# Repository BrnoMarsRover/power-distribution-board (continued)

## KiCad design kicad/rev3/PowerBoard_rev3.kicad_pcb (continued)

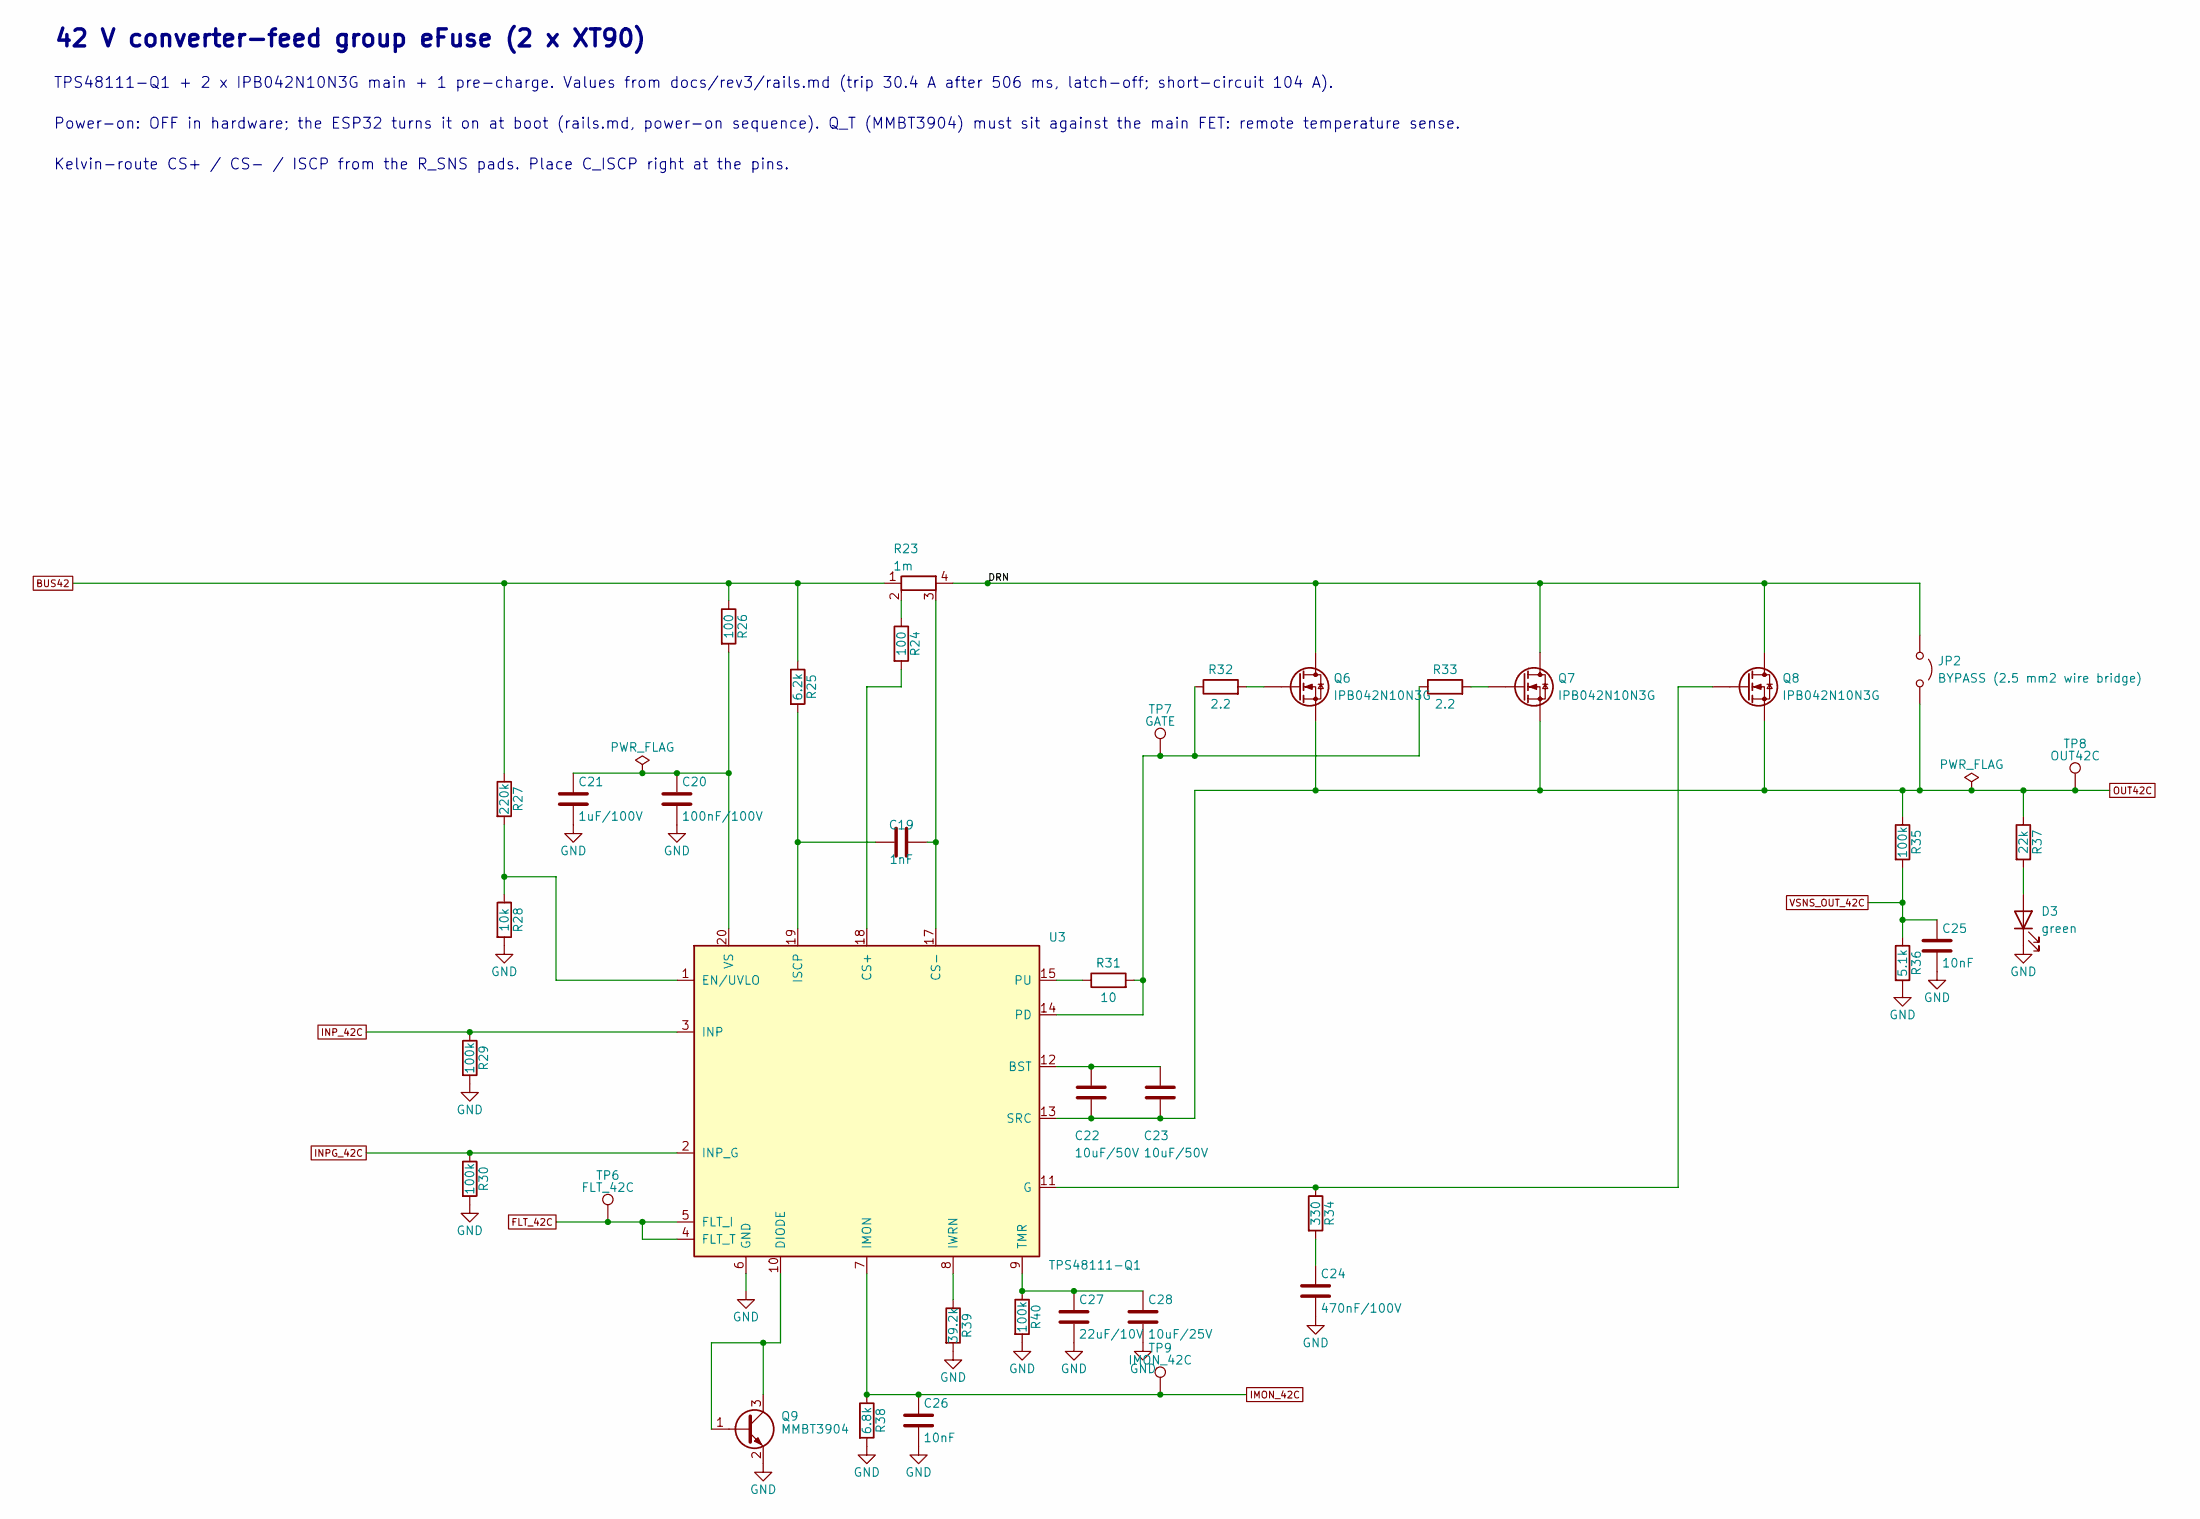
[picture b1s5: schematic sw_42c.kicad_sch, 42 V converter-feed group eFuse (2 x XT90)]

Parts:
C19: 1nF; C_0603_1608Metric_Pad1.08x0.95mm_HandSolder; MPN C0603C102J5GACTU
C20: 100nF/100V; C_0603_1608Metric_Pad1.08x0.95mm_HandSolder; MPN CL10B104KC8NNNC
C21: 1uF/100V; C_1206_3216Metric_Pad1.33x1.80mm_HandSolder; MPN GRM31CR72A105KA01L
C22, C23: 10uF/50V; C_1210_3225Metric_Pad1.33x2.70mm_HandSolder; MPN CL32B106KBJNNNE
C24: 470nF/100V; C_1206_3216Metric_Pad1.33x1.80mm_HandSolder; MPN C1206C474K1RACTU
C25, C26: 10nF; C_0603_1608Metric_Pad1.08x0.95mm_HandSolder; MPN CL10B103KB8NNNC
C27: 22uF/10V; C_1206_3216Metric_Pad1.33x1.80mm_HandSolder; MPN CL31B226KPHNNNE
C28: 10uF/25V; C_1206_3216Metric_Pad1.33x1.80mm_HandSolder; MPN CL31A106KAHNNNE
D3: green; LED_0805_2012Metric_Pad1.15x1.40mm_HandSolder; MPN APT2012SGC
JP2: BYPASS (2.5 mm2 wire bridge); WireBridge_2.5mm2_P7.62mm; MPN none: solid copper wire bridge, fitted 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
Q6, Q7, Q8: IPB042N10N3G; TO-263-2; MPN IPB042N10N3GATMA1
Q9: MMBT3904; SOT-23; MPN MMBT3904LT1G
R23: 1m; R_Bourns_CSS2H-2512_Kelvin; MPN CSS2H-2512R-1L00F
R24, R26: 100; R_0603_1608Metric_Pad0.98x0.95mm_HandSolder; MPN RC0603FR-07100RL
R25: 6.2k; R_0603_1608Metric_Pad0.98x0.95mm_HandSolder; MPN RC0603FR-076K2L
R27: 220k; R_0603_1608Metric_Pad0.98x0.95mm_HandSolder; MPN RC0603FR-07220KL
R28: 10k; R_0603_1608Metric_Pad0.98x0.95mm_HandSolder; MPN RC0603FR-0710KL
R29, R30, R35, R40: 100k; R_0603_1608Metric_Pad0.98x0.95mm_HandSolder; MPN RC0603FR-07100KL
R31: 10; R_0603_1608Metric_Pad0.98x0.95mm_HandSolder; MPN RC0603FR-0710RL
R32, R33: 2.2; R_0603_1608Metric_Pad0.98x0.95mm_HandSolder; MPN RC0603FR-072R2L
R34: 330; R_0603_1608Metric_Pad0.98x0.95mm_HandSolder; MPN RC0603FR-07330RL
R36: 5.1k; R_0603_1608Metric_Pad0.98x0.95mm_HandSolder; MPN RC0603FR-075K1L
R37: 22k; R_1206_3216Metric_Pad1.30x1.75mm_HandSolder; MPN RC1206FR-0722KL
R38: 6.8k; R_0603_1608Metric_Pad0.98x0.95mm_HandSolder; MPN RC0603FR-076K8L
R39: 39.2k; R_0603_1608Metric_Pad0.98x0.95mm_HandSolder; MPN RC0603FR-1339K2L
TP6: FLT_42C; TestPoint_Pad_D1.5mm; MPN none: PCB pad
TP7: GATE; TestPoint_Pad_D1.5mm; MPN none: PCB pad
TP8: OUT42C; TestPoint_Pad_D1.5mm; MPN none: PCB pad
TP9: IMON_42C; TestPoint_Pad_D1.5mm; MPN none: PCB pad
U3: TPS48111-Q1; TI_DGX0019A_VSSOP-19; MPN TPS48111LQDGXRQ1

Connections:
/42 V converter-feed group eFuse (2 x XT90)/DRN: JP2.1 (A), Q6.2 (D), Q7.2 (D), Q8.2 (D), R23.4
BUS42: R23.1, R25.1, R26.1, R27.1; also elsewhere on the board
FLT_42C: TP6.1, U3.4 (FLT_T), U3.5 (FLT_I); also elsewhere on the board
GND: C20.2, C21.2, C24.2, C25.2, C26.2, C27.2, C28.2, D3.1 (K), Q9.2 (E), R28.2, R29.2, R30.2, R36.2, R38.2, R39.2, R40.2, U3.6 (GND); also elsewhere on the board
IMON_42C: C26.1, R38.1, TP9.1, U3.7 (IMON); also elsewhere on the board
INPG_42C: R30.1, U3.2 (INP_G); also elsewhere on the board
INP_42C: R29.1, U3.3 (INP); also elsewhere on the board
unnamed: C24.1, R34.2
unnamed: D3.2 (A), R37.2
unnamed: Q6.1 (G), R32.2
unnamed: Q7.1 (G), R33.2
unnamed: Q8.1 (G), R34.1, U3.11 (G)
unnamed: Q9.1 (B), Q9.3 (C), U3.10 (DIODE)
unnamed: R23.2, R24.1
unnamed: C22.1, C23.1, U3.12 (BST)
unnamed: R24.2, U3.18 (CS+)
unnamed: C19.2, R23.3, U3.17 (CS-)
unnamed: R27.2, R28.1, U3.1 (EN/UVLO)
unnamed: C19.1, R25.2, U3.19 (ISCP)
unnamed: R39.1, U3.8 (IWRN)
unnamed: R31.2, R32.1, R33.1, TP7.1, U3.14 (PD)
unnamed: R31.1, U3.15 (PU)
unnamed: C27.1, C28.1, R40.1, U3.9 (TMR)
unnamed: C20.1, C21.1, R26.2, U3.20 (VS)
OUT42C: C22.2, C23.2, JP2.2 (B), Q6.3 (S), Q7.3 (S), Q8.3 (S), R35.1, R37.1, TP8.1, U3.13 (SRC); also elsewhere on the board
VSNS_OUT_42C: C25.1, R35.2, R36.1; also elsewhere on the board

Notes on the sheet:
42 V converter-feed group eFuse (2 x XT90)
Power-on: OFF in hardware; the ESP32 turns it on at boot (rails.md, power-on sequence). Q_T (MMBT3904) must sit against the main FET: remote temperature sense.
Kelvin-route CS+ / CS- / ISCP from the R_SNS pads. Place C_ISCP right at the pins.
TPS48111-Q1 + 2 x IPB042N10N3G main + 1 pre-charge. Values from docs/rev3/rails.md (trip 30.4 A after 506 ms, latch-off; short-circuit 104 A).

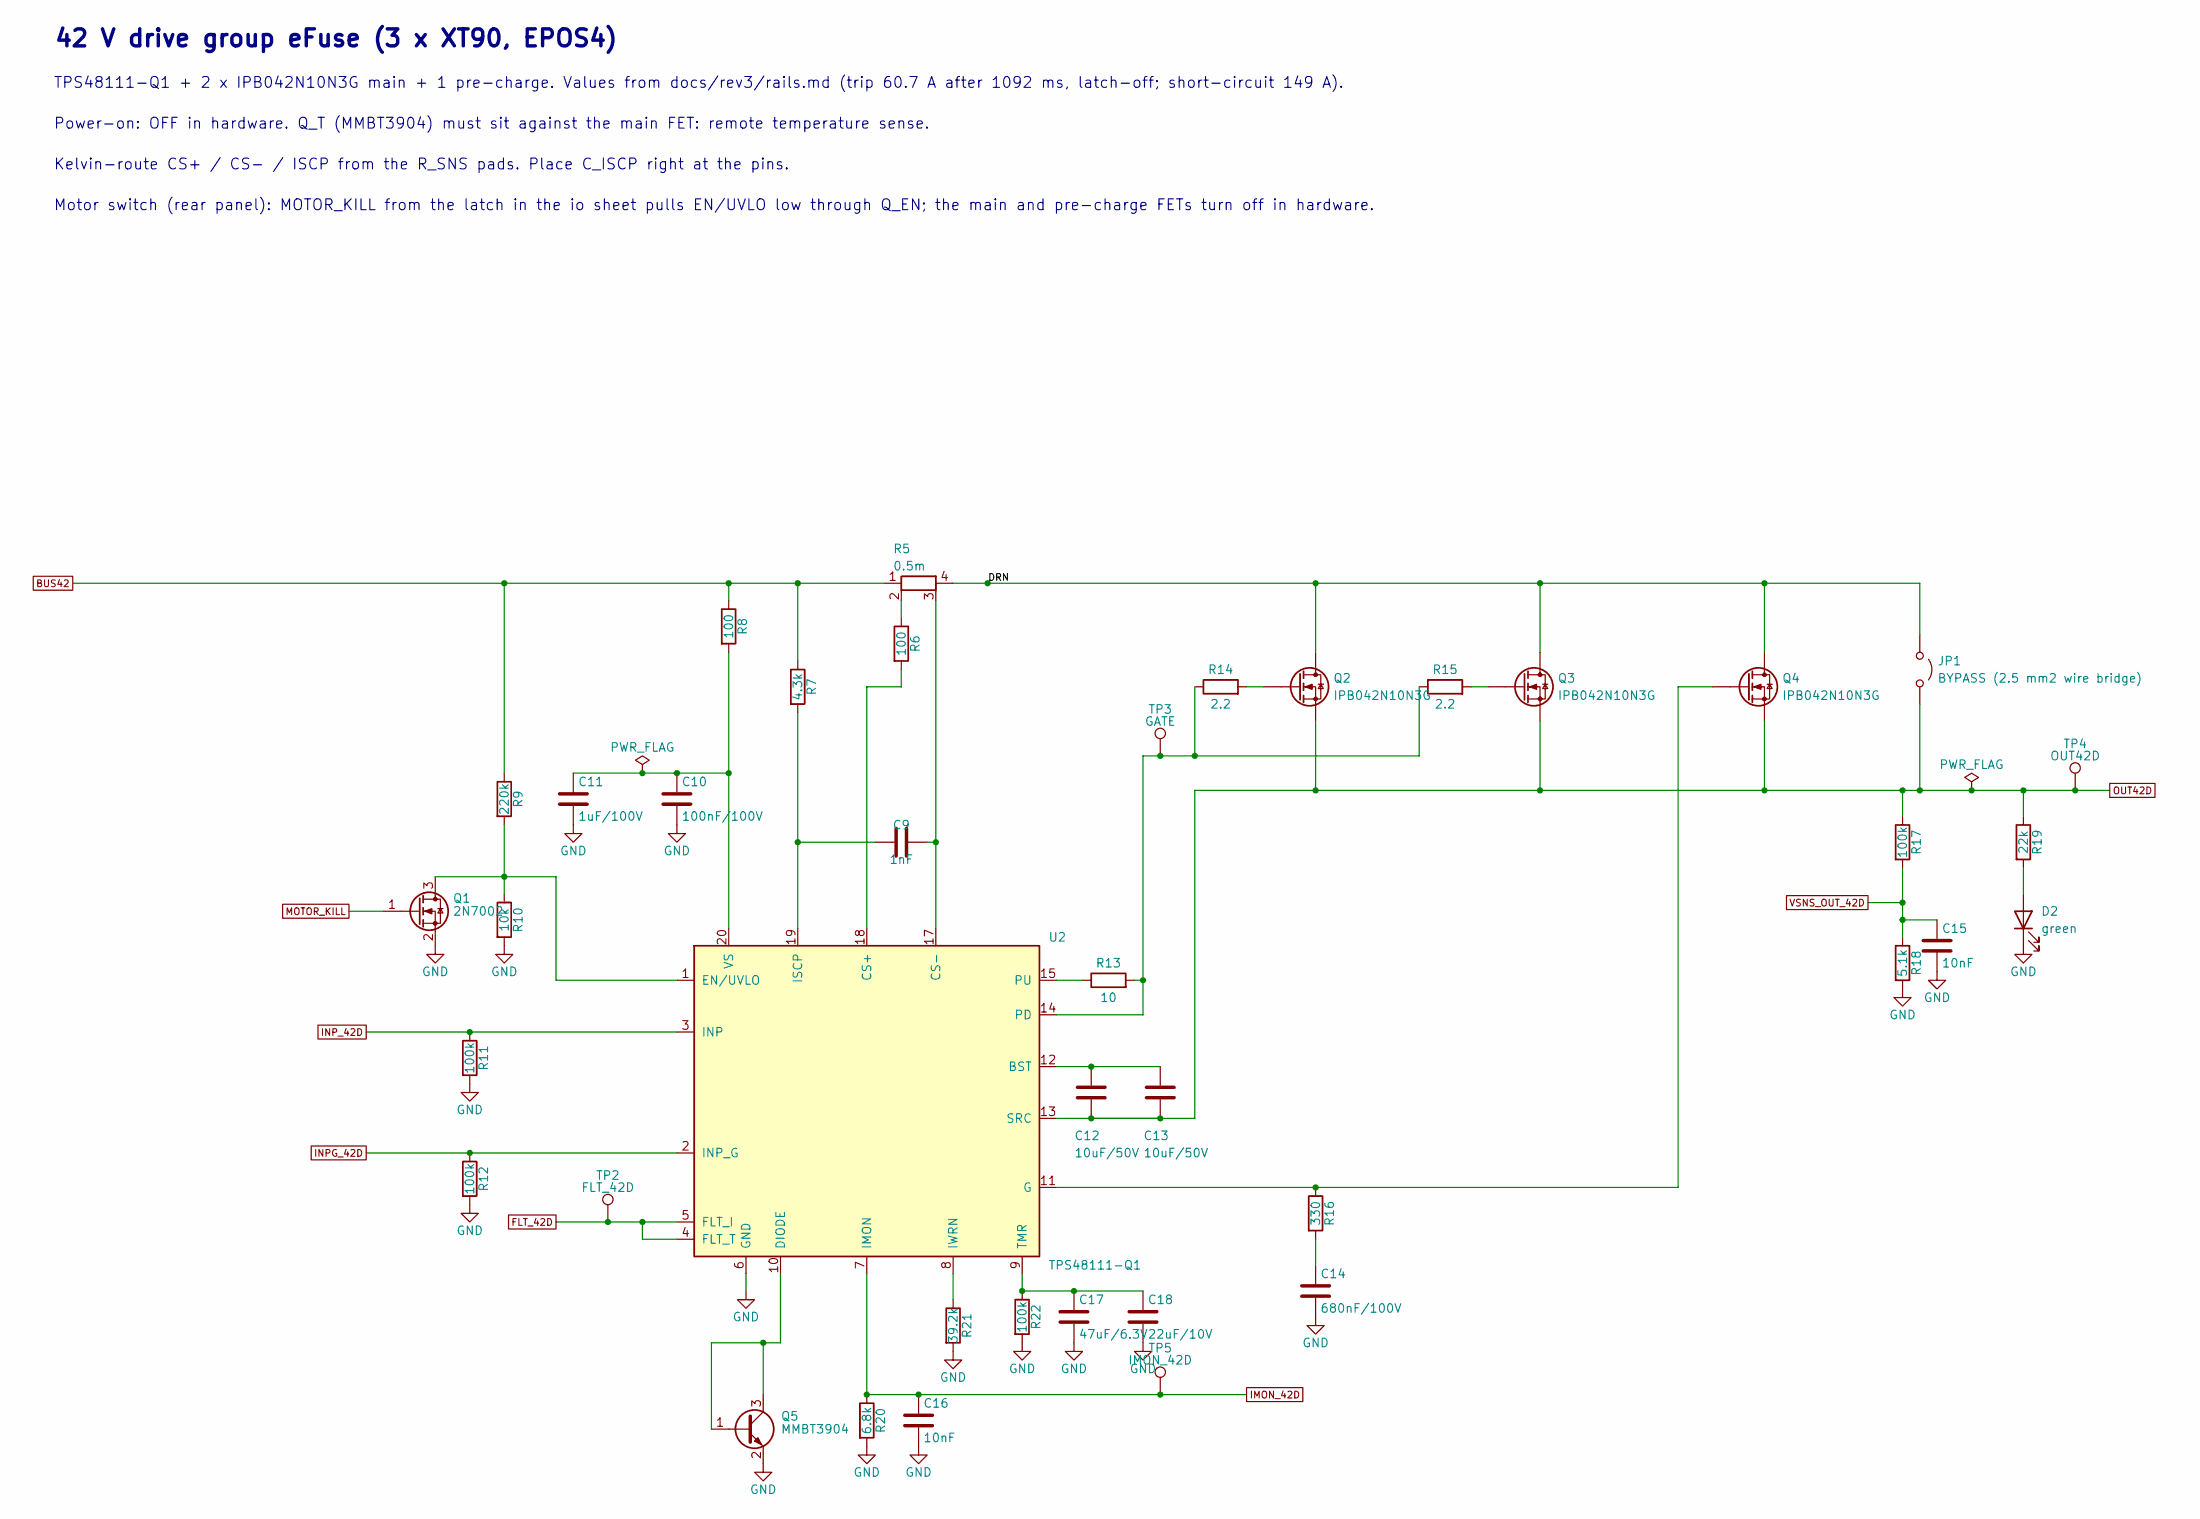
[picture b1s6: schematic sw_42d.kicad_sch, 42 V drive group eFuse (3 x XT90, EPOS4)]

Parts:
C9: 1nF; C_0603_1608Metric_Pad1.08x0.95mm_HandSolder; MPN C0603C102J5GACTU
C10: 100nF/100V; C_0603_1608Metric_Pad1.08x0.95mm_HandSolder; MPN CL10B104KC8NNNC
C11: 1uF/100V; C_1206_3216Metric_Pad1.33x1.80mm_HandSolder; MPN GRM31CR72A105KA01L
C12, C13: 10uF/50V; C_1210_3225Metric_Pad1.33x2.70mm_HandSolder; MPN CL32B106KBJNNNE
C14: 680nF/100V; C_1206_3216Metric_Pad1.33x1.80mm_HandSolder; MPN C3216X7R2A684K160AA
C15, C16: 10nF; C_0603_1608Metric_Pad1.08x0.95mm_HandSolder; MPN CL10B103KB8NNNC
C17: 47uF/6.3V; C_1206_3216Metric_Pad1.33x1.80mm_HandSolder; MPN CL31A476MQHNNNE
C18: 22uF/10V; C_1206_3216Metric_Pad1.33x1.80mm_HandSolder; MPN CL31B226KPHNNNE
D2: green; LED_0805_2012Metric_Pad1.15x1.40mm_HandSolder; MPN APT2012SGC
JP1: BYPASS (2.5 mm2 wire bridge); WireBridge_2.5mm2_P7.62mm; MPN none: solid copper wire bridge, fitted 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
Q1: 2N7002; SOT-23; MPN 2N7002LT1G
Q2, Q3, Q4: IPB042N10N3G; TO-263-2; MPN IPB042N10N3GATMA1
Q5: MMBT3904; SOT-23; MPN MMBT3904LT1G
R5: 0.5m; R_Bourns_CSS2H-2512_Kelvin; MPN CSS2H-2512R-L500F
R6, R8: 100; R_0603_1608Metric_Pad0.98x0.95mm_HandSolder; MPN RC0603FR-07100RL
R7: 4.3k; R_0603_1608Metric_Pad0.98x0.95mm_HandSolder; MPN RC0603FR-074K3L
R9: 220k; R_0603_1608Metric_Pad0.98x0.95mm_HandSolder; MPN RC0603FR-07220KL
R10: 10k; R_0603_1608Metric_Pad0.98x0.95mm_HandSolder; MPN RC0603FR-0710KL
R11, R12, R17, R22: 100k; R_0603_1608Metric_Pad0.98x0.95mm_HandSolder; MPN RC0603FR-07100KL
R13: 10; R_0603_1608Metric_Pad0.98x0.95mm_HandSolder; MPN RC0603FR-0710RL
R14, R15: 2.2; R_0603_1608Metric_Pad0.98x0.95mm_HandSolder; MPN RC0603FR-072R2L
R16: 330; R_0603_1608Metric_Pad0.98x0.95mm_HandSolder; MPN RC0603FR-07330RL
R18: 5.1k; R_0603_1608Metric_Pad0.98x0.95mm_HandSolder; MPN RC0603FR-075K1L
R19: 22k; R_1206_3216Metric_Pad1.30x1.75mm_HandSolder; MPN RC1206FR-0722KL
R20: 6.8k; R_0603_1608Metric_Pad0.98x0.95mm_HandSolder; MPN RC0603FR-076K8L
R21: 39.2k; R_0603_1608Metric_Pad0.98x0.95mm_HandSolder; MPN RC0603FR-1339K2L
TP2: FLT_42D; TestPoint_Pad_D1.5mm; MPN none: PCB pad
TP3: GATE; TestPoint_Pad_D1.5mm; MPN none: PCB pad
TP4: OUT42D; TestPoint_Pad_D1.5mm; MPN none: PCB pad
TP5: IMON_42D; TestPoint_Pad_D1.5mm; MPN none: PCB pad
U2: TPS48111-Q1; TI_DGX0019A_VSSOP-19; MPN TPS48111LQDGXRQ1

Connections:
/42 V drive group eFuse (3 x XT90, EPOS4)/DRN: JP1.1 (A), Q2.2 (D), Q3.2 (D), Q4.2 (D), R5.4
BUS42: R5.1, R7.1, R8.1, R9.1; also elsewhere on the board
FLT_42D: TP2.1, U2.4 (FLT_T), U2.5 (FLT_I); also elsewhere on the board
GND: C10.2, C11.2, C14.2, C15.2, C16.2, C17.2, C18.2, D2.1 (K), Q1.2 (S), Q5.2 (E), R10.2, R11.2, R12.2, R18.2, R20.2, R21.2, R22.2, U2.6 (GND); also elsewhere on the board
IMON_42D: C16.1, R20.1, TP5.1, U2.7 (IMON); also elsewhere on the board
INPG_42D: R12.1, U2.2 (INP_G); also elsewhere on the board
INP_42D: R11.1, U2.3 (INP); also elsewhere on the board
MOTOR_KILL: Q1.1 (G); also elsewhere on the board
unnamed: C14.1, R16.2
unnamed: D2.2 (A), R19.2
unnamed: Q1.3 (D), R9.2, R10.1, U2.1 (EN/UVLO)
unnamed: Q2.1 (G), R14.2
unnamed: Q3.1 (G), R15.2
unnamed: Q4.1 (G), R16.1, U2.11 (G)
unnamed: Q5.1 (B), Q5.3 (C), U2.10 (DIODE)
unnamed: R5.2, R6.1
unnamed: C12.1, C13.1, U2.12 (BST)
unnamed: R6.2, U2.18 (CS+)
unnamed: C9.2, R5.3, U2.17 (CS-)
unnamed: C9.1, R7.2, U2.19 (ISCP)
unnamed: R21.1, U2.8 (IWRN)
unnamed: R13.2, R14.1, R15.1, TP3.1, U2.14 (PD)
unnamed: R13.1, U2.15 (PU)
unnamed: C17.1, C18.1, R22.1, U2.9 (TMR)
unnamed: C10.1, C11.1, R8.2, U2.20 (VS)
OUT42D: C12.2, C13.2, JP1.2 (B), Q2.3 (S), Q3.3 (S), Q4.3 (S), R17.1, R19.1, TP4.1, U2.13 (SRC); also elsewhere on the board
VSNS_OUT_42D: C15.1, R17.2, R18.1; also elsewhere on the board

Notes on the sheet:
Motor switch (rear panel): MOTOR_KILL from the latch in the io sheet pulls EN/UVLO low through Q_EN; the main and pre-charge FETs turn off in hardware.
TPS48111-Q1 + 2 x IPB042N10N3G main + 1 pre-charge. Values from docs/rev3/rails.md (trip 60.7 A after 1092 ms, latch-off; short-circuit 149 A).
Power-on: OFF in hardware. Q_T (MMBT3904) must sit against the main FET: remote temperature sense.
Kelvin-route CS+ / CS- / ISCP from the R_SNS pads. Place C_ISCP right at the pins.
42 V drive group eFuse (3 x XT90, EPOS4)

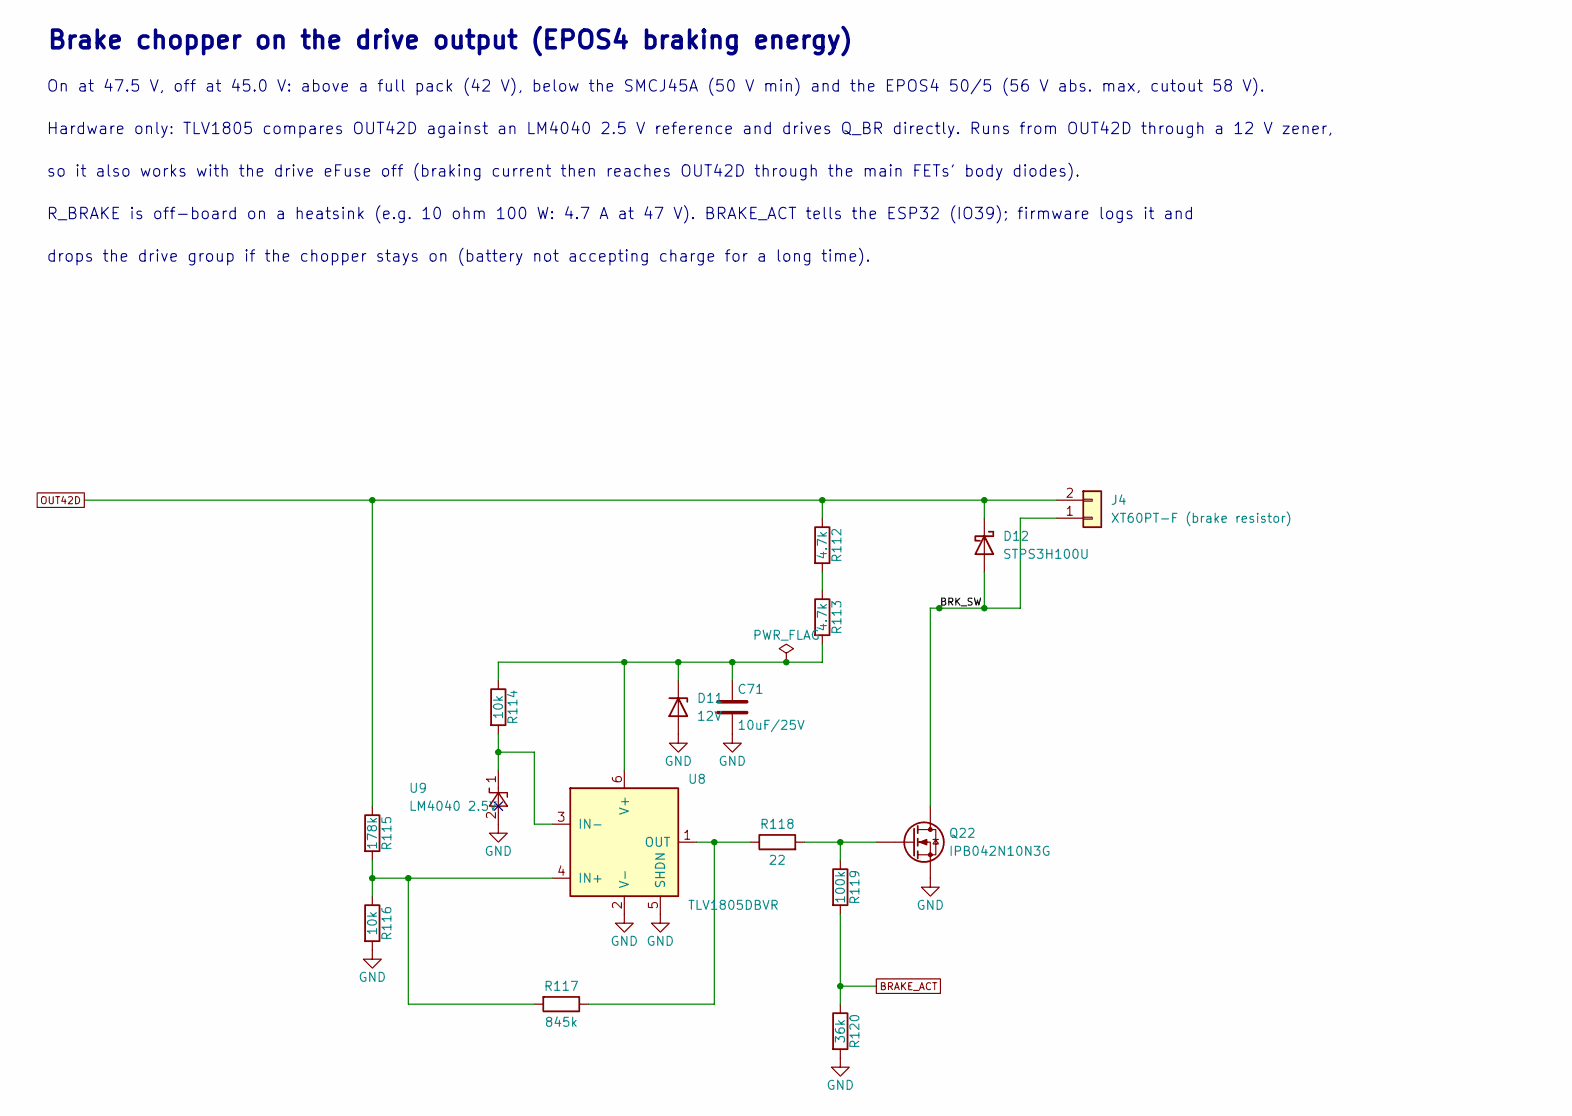
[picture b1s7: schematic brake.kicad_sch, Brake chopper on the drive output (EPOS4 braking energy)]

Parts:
C71: 10uF/25V; C_1206_3216Metric_Pad1.33x1.80mm_HandSolder; MPN CL31A106KAHNNNE
D11: 12V; D_SOD-123; MPN MMSZ5242BT1G
D12: STPS3H100U; D_SMB; MPN STPS3H100U
J4: XT60PT-F (brake resistor); AMASS_XT60-F_1x02_P7.20mm_Vertical; MPN XT60PT-F
Q22: IPB042N10N3G; TO-263-2; MPN IPB042N10N3GATMA1
R112, R113: 4.7k; R_1206_3216Metric_Pad1.30x1.75mm_HandSolder; MPN RC1206FR-074K7L
R114, R116: 10k; R_0603_1608Metric_Pad0.98x0.95mm_HandSolder; MPN RC0603FR-0710KL
R115: 178k; R_1206_3216Metric_Pad1.30x1.75mm_HandSolder; MPN RC1206FR-07178KL
R117: 845k; R_0603_1608Metric_Pad0.98x0.95mm_HandSolder; MPN RC0603FR-07845KL
R118: 22; R_0603_1608Metric_Pad0.98x0.95mm_HandSolder; MPN RC0603FR-0722RL
R119: 100k; R_0603_1608Metric_Pad0.98x0.95mm_HandSolder; MPN RC0603FR-07100KL
R120: 36k; R_0603_1608Metric_Pad0.98x0.95mm_HandSolder; MPN RC0603FR-0736KL
U8: TLV1805DBVR; SOT-23-6; MPN TLV1805DBVR
U9: LM4040 2.5V; SOT-23; MPN LM4040B25IDBZR

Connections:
/Brake chopper on the drive output (EPOS4 braking energy)/BRK_SW: D12.2 (A), J4.1 (-), Q22.2 (D)
BRAKE_ACT: R119.2, R120.1; also elsewhere on the board
GND: C71.2, D11.2 (A), Q22.3 (S), R116.2, R120.2, U8.2 (V-), U8.5 (SHDN), U9.2 (A); also elsewhere on the board
unnamed: C71.1, D11.1 (K), R113.2, R114.1, U8.6 (V+)
unnamed: Q22.1 (G), R118.2, R119.1
unnamed: R112.2, R113.1
unnamed: R115.2, R116.1, R117.2, U8.4 (IN+)
unnamed: R114.2, U8.3 (IN-), U9.1 (K)
unnamed: R117.1, R118.1, U8.1 (OUT)
OUT42D: D12.1 (K), J4.2 (+), R112.1, R115.1; also elsewhere on the board

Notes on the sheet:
so it also works with the drive eFuse off (braking current then reaches OUT42D through the main FETs' body diodes).
On at 47.5 V, off at 45.0 V: above a full pack (42 V), below the SMCJ45A (50 V min) and the EPOS4 50/5 (56 V abs. max, cutout 58 V).
Brake chopper on the drive output (EPOS4 braking energy)
drops the drive group if the chopper stays on (battery not accepting charge for a long time).
Hardware only: TLV1805 compares OUT42D against an LM4040 2.5 V reference and drives Q_BR directly. Runs from OUT42D through a 12 V zener,
R_BRAKE is off-board on a heatsink (e.g. 10 ohm 100 W: 4.7 A at 47 V). BRAKE_ACT tells the ESP32 (IO39); firmware logs it and

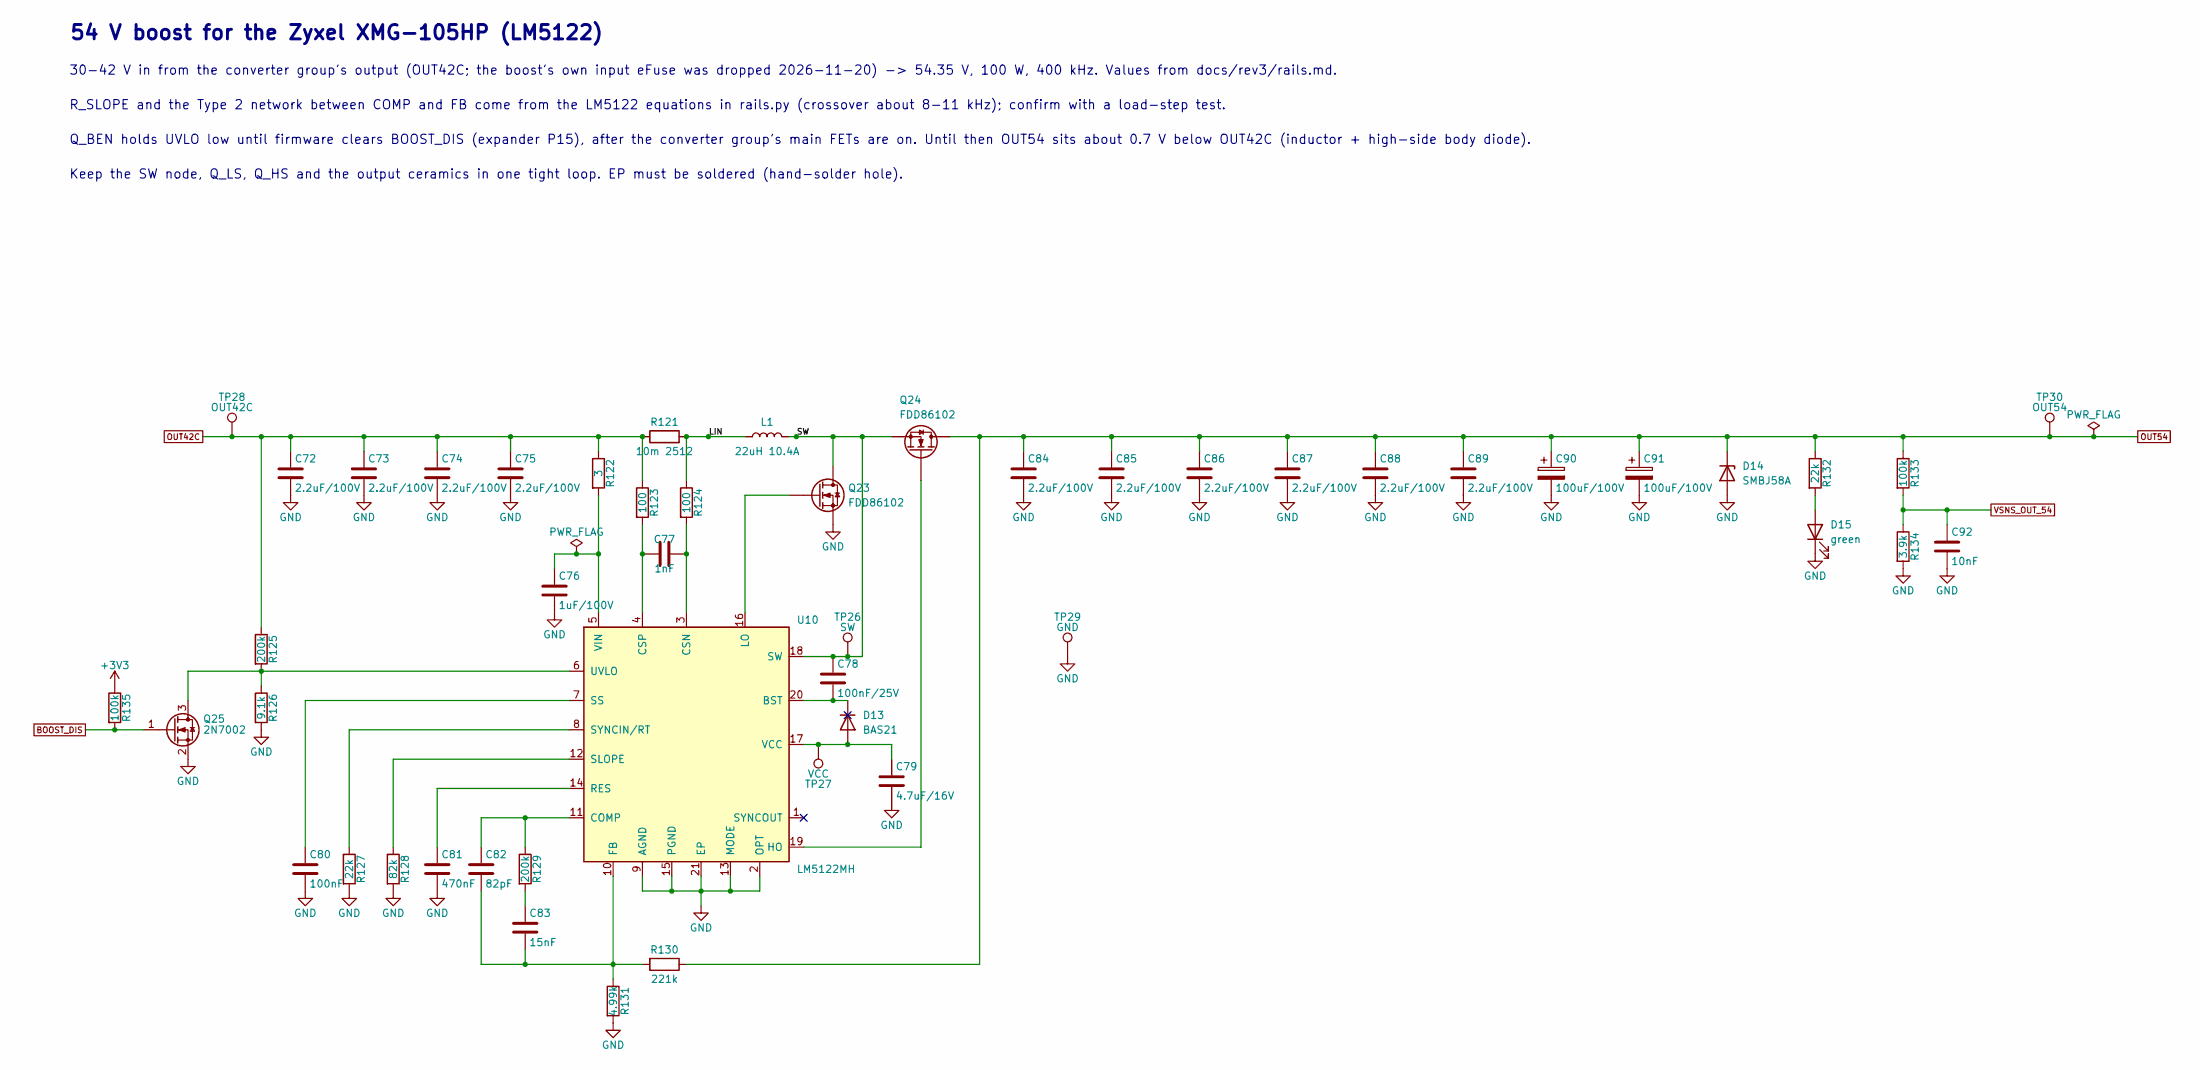
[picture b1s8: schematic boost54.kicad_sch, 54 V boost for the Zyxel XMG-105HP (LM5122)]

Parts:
C72, C73, C74, C75, C84, C85, C86, C87, C88, C89: 2.2uF/100V; C_1210_3225Metric_Pad1.33x2.70mm_HandSolder; MPN C1210C225K1RACTU
C76: 1uF/100V; C_1206_3216Metric_Pad1.33x1.80mm_HandSolder; MPN C1206C105K1RACTU
C77: 1nF; C_0603_1608Metric_Pad1.08x0.95mm_HandSolder; MPN C0603C102J5GACTU
C78: 100nF/25V; C_0603_1608Metric_Pad1.08x0.95mm_HandSolder; MPN C0603C104K5RACTU
C79: 4.7uF/16V; C_0805_2012Metric_Pad1.18x1.45mm_HandSolder; MPN CL21B475KOFNNNE
C80: 100nF; C_0603_1608Metric_Pad1.08x0.95mm_HandSolder; MPN C0603C104K5RACTU
C81: 470nF; C_0603_1608Metric_Pad1.08x0.95mm_HandSolder; MPN CL10B474KA8NNNC
C82: 82pF; C_0603_1608Metric_Pad1.08x0.95mm_HandSolder; MPN C0603C820J5GACTU
C83: 15nF; C_0603_1608Metric_Pad1.08x0.95mm_HandSolder; MPN CL10B153KB8NNNC
C90, C91: 100uF/100V; CP_Radial_D12.5mm_P5.00mm; MPN EEU-FC2A101
C92: 10nF; C_0603_1608Metric_Pad1.08x0.95mm_HandSolder; MPN CL10B103KB8NNNC
D13: BAS21; SOT-23; MPN BAS21-7-F
D14: SMBJ58A; D_SMB; MPN SMBJ58A-13-F
D15: green; LED_0805_2012Metric_Pad1.15x1.40mm_HandSolder; MPN APT2012SGC
L1: 22uH 10.4A; L_Coilcraft_MSS1583-XXX; MPN MSS1583-223MED
Q23, Q24: FDD86102; TO-252-2; MPN FDD86102
Q25: 2N7002; SOT-23; MPN 2N7002LT1G
R121: 10m 2512; R_2512_6332Metric_Pad1.40x3.35mm_HandSolder; MPN WSL2512R0100FEA
R122: 3; R_0603_1608Metric_Pad0.98x0.95mm_HandSolder; MPN ERJ-3RQF3R0V
R123, R124: 100; R_0603_1608Metric_Pad0.98x0.95mm_HandSolder; MPN RC0603FR-07100RL
R125, R129: 200k; R_0603_1608Metric_Pad0.98x0.95mm_HandSolder; MPN RC0603FR-07200KL
R126: 9.1k; R_0603_1608Metric_Pad0.98x0.95mm_HandSolder; MPN RC0603FR-079K1L
R127: 22k; R_0603_1608Metric_Pad0.98x0.95mm_HandSolder; MPN RC0603FR-0722KL
R128: 82k; R_0603_1608Metric_Pad0.98x0.95mm_HandSolder; MPN RC0603FR-0782KL
R130: 221k; R_0603_1608Metric_Pad0.98x0.95mm_HandSolder; MPN RC0603FR-07221KL
R131: 4.99k; R_0603_1608Metric_Pad0.98x0.95mm_HandSolder; MPN RC0603FR-074K99L
R132: 22k; R_1206_3216Metric_Pad1.30x1.75mm_HandSolder; MPN RC1206FR-0722KL
R133, R135: 100k; R_0603_1608Metric_Pad0.98x0.95mm_HandSolder; MPN RC0603FR-07100KL
R134: 3.9k; R_0603_1608Metric_Pad0.98x0.95mm_HandSolder; MPN RC0603FR-073K9L
TP26: SW; TestPoint_Pad_D1.5mm; MPN none: PCB pad
TP27: VCC; TestPoint_Pad_D1.5mm; MPN none: PCB pad
TP28: OUT42C; TestPoint_Pad_D1.5mm; MPN none: PCB pad
TP29: GND; TestPoint_Keystone_5015_Micro_Mini; MPN 5015
TP30: OUT54; TestPoint_Pad_D1.5mm; MPN none: PCB pad
U10: LM5122MH; HTSSOP-20-1EP_4.4x6.5mm_P0.65mm_EP3.4x6.5mm_Mask2.96x2.96mm; MPN LM5122MHX/NOPB

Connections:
+3V3: R135.1; also elsewhere on the board
/54 V boost for the Zyxel XMG-105HP (LM5122)/LIN: L1.1, R121.2, R124.1
/54 V boost for the Zyxel XMG-105HP (LM5122)/SW: C78.1, L1.2, Q23.2 (D), Q24.3 (S), TP26.1, U10.18 (SW)
BOOST_DIS: Q25.1 (G), R135.2; also elsewhere on the board
GND: C72.2, C73.2, C74.2, C75.2, C76.2, C79.2, C80.2, C81.2, C84.2, C85.2, C86.2, C87.2, C88.2, C89.2, C90.2, C91.2, C92.2, D14.2 (A), D15.1 (K), Q23.3 (S), Q25.2 (S), R126.2, R127.2, R128.2, R131.2, R134.2, TP29.1, U10.2 (OPT), U10.9 (AGND), U10.13 (MODE), U10.15 (PGND), U10.21 (EP); also elsewhere on the board
unnamed: C83.1, R129.2
unnamed: C79.1, D13.1 (A), TP27.1, U10.17 (VCC)
unnamed: C78.2, D13.3 (K), U10.20 (BST)
unnamed: D15.2 (A), R132.2
unnamed: Q23.1 (G), U10.16 (LO)
unnamed: Q24.1 (G), U10.19 (HO)
unnamed: Q25.3 (D), R125.2, R126.1, U10.6 (UVLO)
unnamed: C82.1, R129.1, U10.11 (COMP)
unnamed: C77.2, R124.2, U10.3 (CSN)
unnamed: C77.1, R123.2, U10.4 (CSP)
unnamed: C82.2, C83.2, R130.2, R131.1, U10.10 (FB)
unnamed: C81.1, U10.14 (RES)
unnamed: R128.1, U10.12 (SLOPE)
unnamed: C80.1, U10.7 (SS)
unnamed: R127.1, U10.8 (SYNCIN/RT)
unnamed: C76.1, R122.2, U10.5 (VIN)
OUT42C: C72.1, C73.1, C74.1, C75.1, R121.1, R122.1, R123.1, R125.1, TP28.1; also elsewhere on the board
OUT54: C84.1, C85.1, C86.1, C87.1, C88.1, C89.1, C90.1, C91.1, D14.1 (K), Q24.2 (D), R130.1, R132.1, R133.1, TP30.1; also elsewhere on the board
VSNS_OUT_54: C92.1, R133.2, R134.1; also elsewhere on the board

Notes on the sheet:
54 V boost for the Zyxel XMG-105HP (LM5122)
R_SLOPE and the Type 2 network between COMP and FB come from the LM5122 equations in rails.py (crossover about 8-11 kHz); confirm with a load-step test.
30-42 V in from the converter group's output (OUT42C; the boost's own input eFuse was dropped 2026-11-20) -> 54.35 V, 100 W, 400 kHz. Values from docs/rev3/rails.md.
Q_BEN holds UVLO low until firmware clears BOOST_DIS (expander P15), after the converter group's main FETs are on. Until then OUT54 sits about 0.7 V below OUT42C (inductor + high-side body diode).
Keep the SW node, Q_LS, Q_HS and the output ceramics in one tight loop. EP must be soldered (hand-solder hole).

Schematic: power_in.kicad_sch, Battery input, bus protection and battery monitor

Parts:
C1, C2: 100uF/100V; CP_Radial_D12.5mm_P5.00mm; MPN EEU-FC2A101
C3, C4, C5, C6: 2.2uF/100V; C_1210_3225Metric_Pad1.33x2.70mm_HandSolder; MPN GRM32ER72A225KA35L
C7, C8: 100nF; C_0603_1608Metric_Pad1.08x0.95mm_HandSolder; MPN C0603C104K5RACTU
D1: SMCJ45A; D_SMC; MPN SMCJ45A
J1: XT90PB-M (battery in); XT90PB-M; MPN XT90PB-M
J2: XT60PT-M (charger in); AMASS_XT60-M_1x02_P7.20mm_Vertical; MPN XT60PT-M
J3: XT60PT-M (pack charge port); AMASS_XT60-M_1x02_P7.20mm_Vertical; MPN XT60PT-M
R1: 2m 5W; R_Bourns_CSS2H-2512_Kelvin; MPN CSS2H-2512K-2L00F
R2, R3: 10; R_0603_1608Metric_Pad0.98x0.95mm_HandSolder; MPN RC0603FR-0710RL
R4: 10k; R_0603_1608Metric_Pad0.98x0.95mm_HandSolder; MPN RC0603FR-0710KL
TP1: GND; TestPoint_Keystone_5015_Micro_Mini; MPN 5015
U1: INA228AIDGSR; TSSOP-10_3x3mm_P0.5mm; MPN INA228AIDGSR

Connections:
+3V3: C8.1, R4.1, U1.6 (VS); also elsewhere on the board
/Battery input, bus protection and battery monitor/CHG_N: J2.1 (-), J3.1 (-)
BUS42: J2.2 (+), R1.4, U1.8 (VBUS); also elsewhere on the board
GND: C1.2, C2.2, C3.2, C4.2, C5.2, C6.2, C8.2, D1.2 (A), J1.2, TP1.1, U1.1 (A1), U1.2 (A0), U1.7 (GND); also elsewhere on the board
I2C_SCL: U1.5 (SCL); also elsewhere on the board
I2C_SDA: U1.4 (SDA); also elsewhere on the board
INA_ALERT: R4.2, U1.3 (~ALERT); also elsewhere on the board
unnamed: R1.2, R2.1
unnamed: R1.3, R3.1
unnamed: C7.1, R2.2, U1.10 (IN+)
unnamed: C7.2, R3.2, U1.9 (IN-)
VBAT: C1.1, C2.1, C3.1, C4.1, C5.1, C6.1, D1.1 (K), J1.1, J3.2 (+), R1.1

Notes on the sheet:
Charging: charger + enters on the bus side of the shunt and leaves through the pack's charge port,
Battery 10S 30-42 V. The pack fuse (58 V rated) and BMS live in the harness, not on this board.
INA228 at 0x40 (A0 = A1 = GND), ADCRANGE = 0 (+-163.84 mV = +-82 A): bus V, current, power, and on-chip charge / energy.
Battery input, bus protection and battery monitor
so the INA228 counts it (net of the rover's own load). Charger - is NOT board GND: CHG_N goes straight to the pack's C-.
R_SHUNT: Bourns CSS2H-2512K, Kelvin land pattern (net-tie footprint). Route SNS_P / SNS_N as a pair from the fingers.
